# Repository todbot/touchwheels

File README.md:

# Touchwheels

Some capacitive sense rotary touchwheels.  

These work by using only three capactive touch pads in a specific interleaved 
geometry and measuring the relative ratio of analog capacitive touch values 
between the pads to compute a distance along the slider. 

### Touchwheels made so far:

* TouchWheelSAO -- [Touchwheel SAO as part of  Hackaday Supercon 2024 badge](https://github.com/todbot/TouchwheelSAO)

* touchwheel0 - [available on Tindie as a kit!](https://www.tindie.com/products/todbot/touchwheel0-capacitive-touch-wheel/)

  Similar to an iPod's wheel, `touchwheel0` is a 30 mm (0.6") diameter 
  [rotary capacitive touch slider](https://onlinedocs.microchip.com/pr/GUID-A8A0085D-58D1-4E41-A07D-B93BFDE11AFE-en-US-4/index.html?GUID-FB5E9311-C731-4326-82D2-CD5F0ED8E378) that can be used with most any microcontroller. It uses three digital GPIO pins and requires no extra components. The included examples in CircuitPython and Arduino show how to turn the raw capacitive touch readings of the three pins into a linear 0-360º angle measurement.

* picoslidertoy - Available at the [picoslidertoy repo](https://github.com/todbot/picoslidertoy)

### Demos:

There are several examples on how to use the touchwheel:

- [demo0](./circuitpython/demo0/code.py) -
    CircuitPython example showing basic concept on touchwheel0
  
- [touchwheel_badgedemo](./circuitpython/touchwheel_badgedemo/code.py) - 
    CircuitPython example for the Hackaday SuperCon 2023 badge (where touchwheel0 PCBs were given away)
    
- [demo_dual](./circuitpython/demo_dual/code.py) - 
    CircuitPython example show two touchwheel0s in use

- more demos coming!

### What's in Tindie touchwheel0 kit: 

The [touchwheel0 kit](https://www.tindie.com/products/todbot/touchwheel0-capacitive-touch-wheel/)
on Tindie comes with:

- touchwheel0 black PCB
- 4 x 1M 0805 SMD resistors (only three needed, one is a spare)
- 1 x 4-pin pin header 

It makes a pretty good "first SMD soldering" exercise as the 0805 resistors 
are relatively big and not very heat sensitive. 

### Demo videos:

- demo dual:
  [(click to view on youtube)](https://www.youtube.com/watch?v=Db7S75eE-G8)

- demo0: 

  https://github.com/todbot/touchwheels/assets/274093/fc2b794f-5dff-42b4-8942-f141de19e4ab

### Useful links:

- [AN2934 - Capacitive Touch Sensor Design Guide (pdf)](https://ww1.microchip.com/downloads/en/Appnotes/Capacitive-Touch-Sensor-Design-Guide-DS00002934-B.pdf)
- [QTAN007 - Buttons, Sliders and Wheels - Sensor Design Guide (pdf)](https://www.mouser.com/pdfDocs/QTouch_QTAN0079.pdf)
- [AT02259: QTouch Schematic and Layout Checklist (pdf)](http://ww1.microchip.com/downloads/en/appnotes/atmel-42094-qtouch-schematic-and-layout-checklist_applicationnote_at02259.pdf)
- [slider generator](https://cooltech.zone/tangara/labs/touchwheel-electrode-tool/)
- [SLAA891B: Automating Capacitive Touch Sensor PCB layouts with OpenSCAD Ti AppNote (pdf)](https://www.ti.com/lit/an/slaa891b/slaa891b.pdf?ts=1725369981627)

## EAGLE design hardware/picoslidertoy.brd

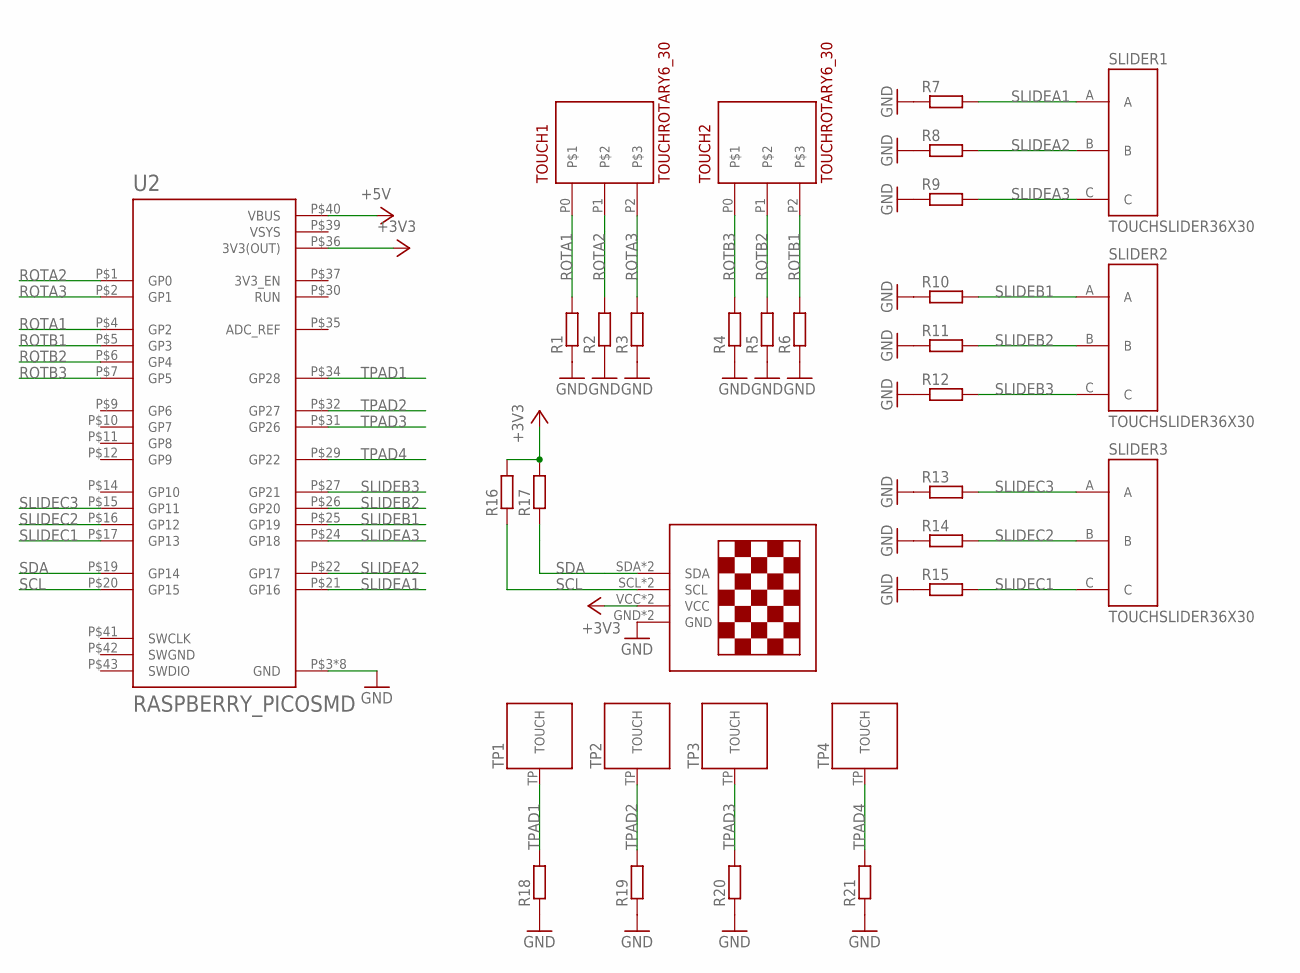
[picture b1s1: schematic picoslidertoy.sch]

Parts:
R1, R2, R3, R4, R5, R6, R7, R8, R9, R10, R11, R12, R13, R14, R15, R16, R17, R18, R19, R20, R21: R-EU_R0805; R0805
SLIDER1, SLIDER2, SLIDER3: TOUCHSLIDER36X30; TOUCHSLIDER3_6X30
SMDBACK2: 13"OLED; 1.3"OLED_SMDBACK
TOUCH1, TOUCH2: TOUCHROTARY6_30; TOUCHROTARY1B
TP1, TP2, TP3, TP4: TOUCHPADA; TOUCHPADA_0.5IN
U2: RASPBERRY_PICOSMD; PICO-PKG-SMD

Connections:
+3V3: R16.2, R17.2, SMDBACK2.VCC, SMDBACK2.VCC_2 (VCC), U2.P$36 (3V3(OUT))
+5V: U2.P$40 (VBUS)
GND: R1.1, R2.1, R3.1, R4.1, R5.1, R6.1, R7.1, R8.1, R9.1, R10.1, R11.1, R12.1, R13.1, R14.1, R15.1, R18.1, R19.1, R20.1, R21.1, SMDBACK2.GND, SMDBACK2.GND_2 (GND), U2.P$3 (GND), U2.P$8 (GND), U2.P$13 (GND), U2.P$18 (GND), U2.P$23 (GND), U2.P$28 (GND), U2.P$33 (GND), U2.P$38 (GND)
ROTA1: R1.2, TOUCH1.P0, U2.P$4 (GP2)
ROTA2: R2.2, TOUCH1.P1, U2.P$1 (GP0)
ROTA3: R3.2, TOUCH1.P2, U2.P$2 (GP1)
ROTB1: R6.2, TOUCH2.P2, U2.P$5 (GP3)
ROTB2: R5.2, TOUCH2.P1, U2.P$6 (GP4)
ROTB3: R4.2, TOUCH2.P0, U2.P$7 (GP5)
SCL: R16.1, SMDBACK2.SCL, SMDBACK2.SCL_2 (SCL), U2.P$20 (GP15)
SDA: R17.1, SMDBACK2.SDA, SMDBACK2.SDA_2 (SDA), U2.P$19 (GP14)
SLIDEA1: R7.2, SLIDER1.A, U2.P$21 (GP16)
SLIDEA2: R8.2, SLIDER1.B, U2.P$22 (GP17)
SLIDEA3: R9.2, SLIDER1.C, U2.P$24 (GP18)
SLIDEB1: R10.2, SLIDER2.A, U2.P$25 (GP19)
SLIDEB2: R11.2, SLIDER2.B, U2.P$26 (GP20)
SLIDEB3: R12.2, SLIDER2.C, U2.P$27 (GP21)
SLIDEC1: R15.2, SLIDER3.C, U2.P$17 (GP13)
SLIDEC2: R14.2, SLIDER3.B, U2.P$16 (GP12)
SLIDEC3: R13.2, SLIDER3.A, U2.P$15 (GP11)
SWGND: U2.P$42 (SWGND)
TPAD1: R18.2, TP1.TP, U2.P$34 (GP28)
TPAD2: R19.2, TP2.TP, U2.P$32 (GP27)
TPAD3: R20.2, TP3.TP, U2.P$31 (GP26)
TPAD4: R21.2, TP4.TP, U2.P$29 (GP22)
VSYS: U2.P$39 (VSYS)

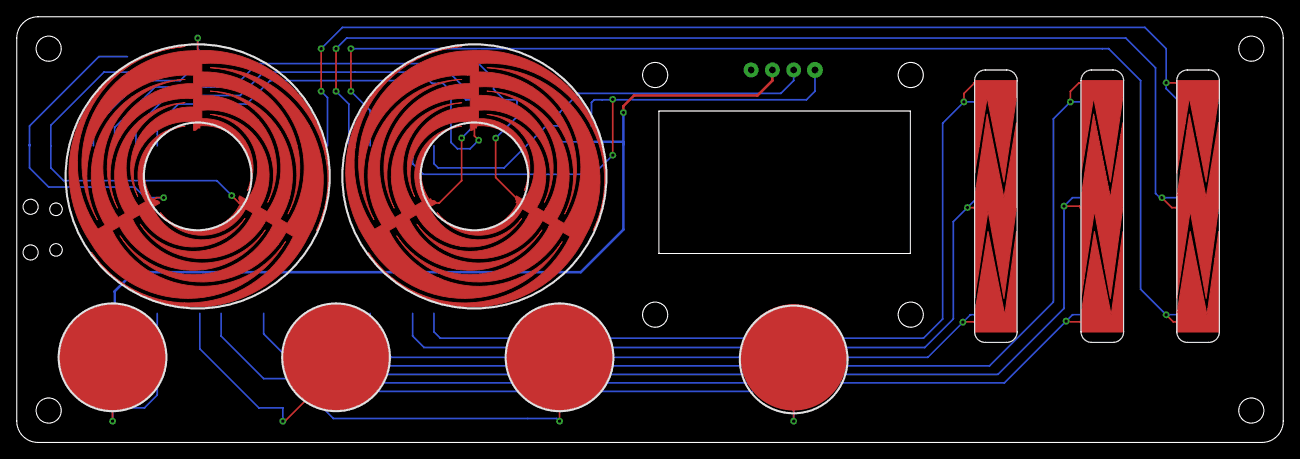
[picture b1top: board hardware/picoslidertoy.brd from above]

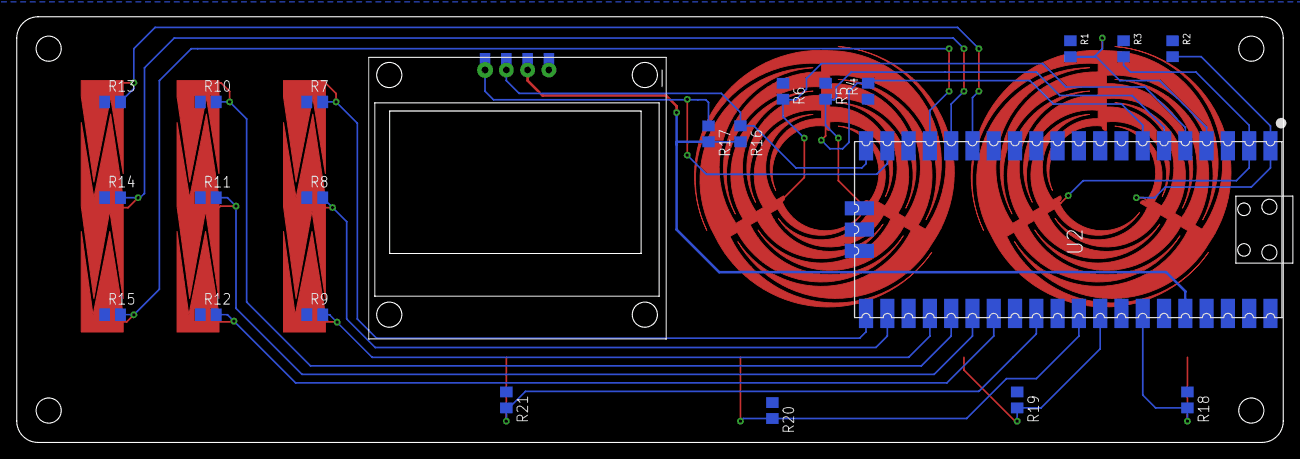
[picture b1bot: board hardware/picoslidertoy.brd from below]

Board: 2 copper layers, 151.0 x 50.7 mm, 32 parts (22 on the bottom side), 23 nets.

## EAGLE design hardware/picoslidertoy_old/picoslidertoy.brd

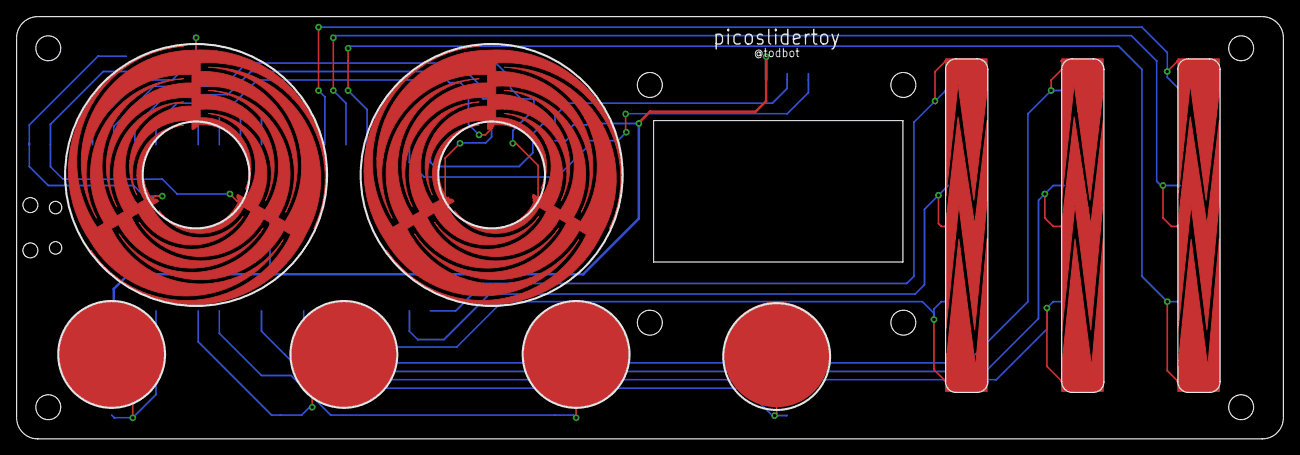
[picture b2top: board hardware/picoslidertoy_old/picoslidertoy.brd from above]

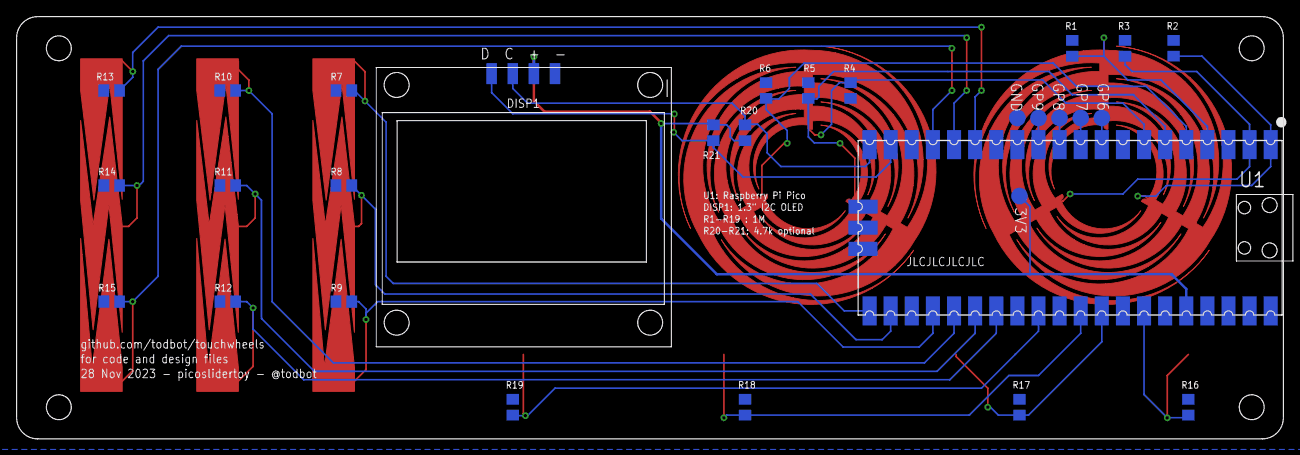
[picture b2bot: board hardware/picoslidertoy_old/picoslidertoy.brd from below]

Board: 2 copper layers, 152.3 x 50.7 mm, 38 parts (28 on the bottom side), 27 nets.

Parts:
3V3: TPTP20R; TP20R
GND: TPTP20R; TP20R
GP6, GP7, GP8, GP9: TPTP20R; TP20R
R1, R2, R3, R4, R5, R6, R7, R8, R9, R10, R11, R12, R13, R14, R15, R16, R17, R18, R19: 1M; R0805
R20, R21: 4.7k; R0805
SLIDER1, SLIDER2, SLIDER3: TOUCHSLIDER36X40; TOUCHSLIDER3_6X40
SMDBACK2: 13"OLEDSMDONLY; 1.3"OLED_SMDBACKONLY
TOUCH1, TOUCH2: TOUCHROTARY6_30; TOUCHROTARY1B
TP1, TP2, TP3, TP4: TOUCHPADA; TOUCHPADA_0.5IN
U1: RASPBERRY_PICOSMD; PICO-PKG-SMD

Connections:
+3V3: 3V3.TP, R20.2, R21.2, SMDBACK2.VCC, U1.P$36
GND: GND.TP, R1.1, R2.1, R3.1, R4.1, R5.1, R6.1, R7.1, R8.1, R9.1, R10.1, R11.1, R12.1, R13.1, R14.1, R15.1, R16.1, R17.1, R18.1, R19.1, SMDBACK2.GND, U1.P$3, U1.P$8, U1.P$13, U1.P$18, U1.P$23, U1.P$28, U1.P$33, U1.P$38
unnamed: GP6.TP, U1.P$9
unnamed: GP7.TP, U1.P$10
unnamed: GP9.TP, U1.P$12
unnamed: GP8.TP, U1.P$11
ROTA1: R1.2, TOUCH1.P0, U1.P$4
ROTA2: R2.2, TOUCH1.P1, U1.P$1
ROTA3: R3.2, TOUCH1.P2, U1.P$2
ROTB1: R6.2, TOUCH2.P2, U1.P$5
ROTB2: R5.2, TOUCH2.P1, U1.P$6
ROTB3: R4.2, TOUCH2.P0, U1.P$7
SCL: R20.1, SMDBACK2.SCL, U1.P$20
SDA: R21.1, SMDBACK2.SDA, U1.P$19
SLIDEA1: R7.2, SLIDER1.A, U1.P$21
SLIDEA2: R8.2, SLIDER1.B, U1.P$22
SLIDEA3: R9.2, SLIDER1.C, U1.P$24
SLIDEB1: R10.2, SLIDER2.A, U1.P$25
SLIDEB2: R11.2, SLIDER2.B, U1.P$26
SLIDEB3: R12.2, SLIDER2.C, U1.P$27
SLIDEC1: R15.2, SLIDER3.C, U1.P$17
SLIDEC2: R14.2, SLIDER3.B, U1.P$16
SLIDEC3: R13.2, SLIDER3.A, U1.P$15
TPAD1: R16.2, TP1.TP, U1.P$34
TPAD2: R17.2, TP2.TP, U1.P$32
TPAD3: R18.2, TP3.TP, U1.P$31
TPAD4: R19.2, TP4.TP, U1.P$29

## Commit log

2023-10-27 touchweel0
2023-11-03 first test python
2023-11-03 update demo0
2023-11-03 small cleanup
2023-11-03 add pdf of sch
2023-11-03 png of pcb
2023-11-03 add image to readme
2023-11-06 put simplified code from HackadayVectorScope repo
2023-11-09 fix comment tabbing
2023-12-04 should finally commit picosolidertoy
2023-12-06 picoslidertoy layout mostly done
2024-03-17 old picoslidertoy sync up, but moved dev to its own repo and kicad
2024-03-23 moved old picoslidertoy idea, new version has its own repo
2024-04-12 add dual touchwheel0 example
2024-04-12 restructure
2024-04-12 Update README.md add demo0 video
2024-04-12 check in start of arduino version
2024-04-12 added some useful links
